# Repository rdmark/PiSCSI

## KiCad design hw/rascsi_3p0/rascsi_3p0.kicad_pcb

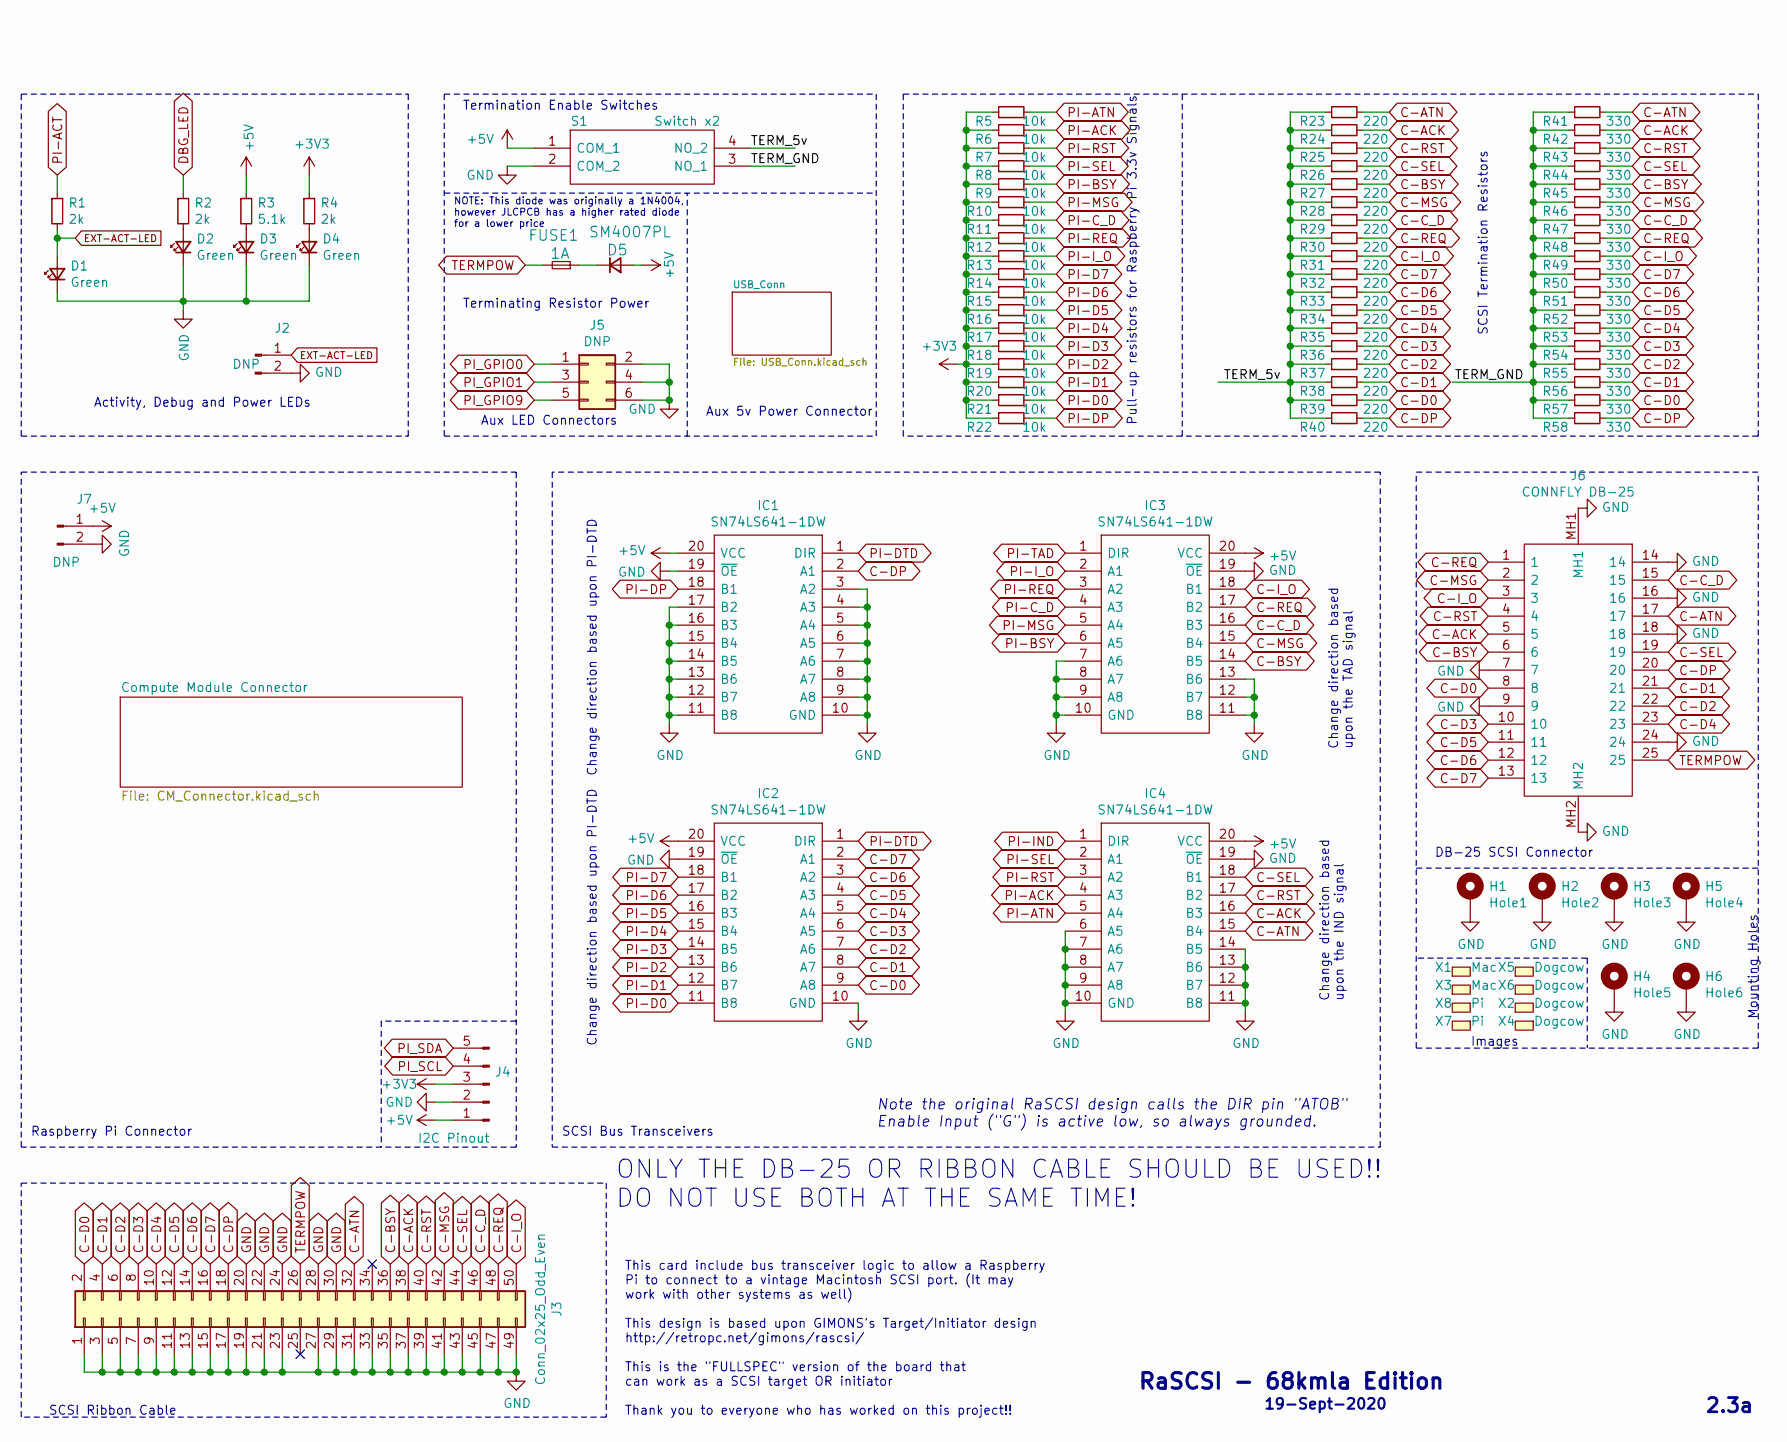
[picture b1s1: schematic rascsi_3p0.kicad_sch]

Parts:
D1, D2, D3, D4: Green; LED_0805_2012Metric; Manufacturer_Part_Number C2297; LCSC C2297
D5: SM4007PL; D_SOD-123F; Manufacturer_Part_Number SM4007PL; LCSC C64898
FUSE1: 1A; Fuse_1206_3216Metric; Manufacturer_Part_Number 12B1100B; LCSC C182974
H1: Hole1; MountingHole_2.7mm_M2.5_Pad_Via; Manufacturer_Part_Number DNP; LCSC DNP
H2: Hole2; MountingHole_2.7mm_M2.5_Pad_Via; Manufacturer_Part_Number DNP; LCSC DNP
H3: Hole3; MountingHole_2.7mm_M2.5_Pad_Via; Manufacturer_Part_Number DNP; LCSC DNP
H4: Hole5; MountingHole_2.7mm_M2.5_Pad_Via; Manufacturer_Part_Number DNP; LCSC DNP
H5: Hole4; MountingHole_2.7mm_M2.5_Pad_Via; Manufacturer_Part_Number DNP; LCSC DNP
H6: Hole6; MountingHole_2.7mm_M2.5_Pad_Via; Manufacturer_Part_Number DNP; LCSC DNP
IC1, IC2, IC3, IC4: SN74LS641-1DW; SOIC127P1030X265-20N; Manufacturer_Part_Number SN74LS641-1DW; LCSC N/A
J2: DNP; PinHeader_1x02_P2.54mm_Horizontal; Manufacturer_Part_Number DNP; LCSC DNP
J3: Conn_02x25_Odd_Even; PinHeader_2x25_P2.54mm_Vertical; Manufacturer_Part_Number C30006; LCSC C30006
J4: I2C Pinout; PinSocket_1x05_P2.54mm_Vertical; Manufacturer_Part_Number C50950; LCSC C50950
J5: DNP; PinHeader_2x03_P2.54mm_Vertical; Manufacturer_Part_Number DNP; LCSC DNP
J6: CONNFLY DB-25; 57489011; Manufacturer_Part_Number DS1037-25FNAKT74-0CC; LCSC C77838
J7: DNP; PinHeader_1x02_P2.54mm_Vertical; Manufacturer_Part_Number DNP; LCSC DNP
R1, R2, R4: 2k; R_0402_1005Metric; Manufacturer_Part_Number 0402WGF2001TCE; LCSC C4109
R3: 5.1k; R_0402_1005Metric; Manufacturer_Part_Number 0402WGF5101TCE; LCSC C25905
R5, R6, R7, R8, R9, R10, R11, R12, R13, R14, R15, R16, R17, R18, R19, R20, R21, R22: 10k; R_0402_1005Metric; Manufacturer_Part_Number 0402WGF1002TCE; LCSC C25744
R23, R24, R25, R26, R27, R28, R29, R30, R31, R32, R33, R34, R35, R36, R37, R38, R39, R40: 220; R_0402_1005Metric; Manufacturer_Part_Number 0402WGF2200TCE; LCSC C25091
R41, R42, R43, R44, R45, R46, R47, R48, R49, R50, R51, R52, R53, R54, R55, R56, R57, R58: 330; R_0402_1005Metric; Manufacturer_Part_Number 0402WGF3300TCE; LCSC C25104
S1: Switch x2; SOIC127P812X230-4N; Manufacturer_Part_Number DSHP02TSGET; LCSC C40735
X1, X3: Mac; mac_happy_small; Manufacturer_Part_Number N/A; LCSC N/A
X2, X4, X5, X6: Dogcow; dogcow; Manufacturer_Part_Number N/A; LCSC N/A
X7: Pi; pi_logo; Manufacturer_Part_Number N/A; LCSC N/A
X8: Pi; scsi_logo; Manufacturer_Part_Number N/A; LCSC N/A

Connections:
+3V3: J4.3, R4.1, R5.1, R6.1, R7.1, R8.1, R9.1, R10.1, R11.1, R12.1, R13.1, R14.1, R15.1, R16.1, R17.1, R18.1, R19.1, R20.1, R21.1, R22.1; also elsewhere on the board
+5V: D5.2 (A), IC1.20 (VCC), IC2.20 (VCC), IC3.20 (VCC), IC4.20 (VCC), J4.1, J7.1, R3.1, S1.1 (COM_1); also elsewhere on the board
/TERM_5v: R23.1, R24.1, R25.1, R26.1, R27.1, R28.1, R29.1, R30.1, R31.1, R32.1, R33.1, R34.1, R35.1, R36.1, R37.1, R38.1, R39.1, R40.1, S1.4 (NO_2)
/TERM_GND: R41.1, R42.1, R43.1, R44.1, R45.1, R46.1, R47.1, R48.1, R49.1, R50.1, R51.1, R52.1, R53.1, R54.1, R55.1, R56.1, R57.1, R58.1, S1.3 (NO_1)
C-ACK: IC4.16 (B3), J3.38, J6.5, R24.2, R42.2
C-ATN: IC4.15 (B4), J3.32, J6.17, R23.2, R41.2
C-BSY: IC3.14 (B5), J3.36, J6.6, R27.2, R45.2
C-C_D: IC3.16 (B3), J3.46, J6.15, R29.2, R47.2
C-D0: IC2.9 (A8), J3.2, J6.8, R39.2, R57.2
C-D1: IC2.8 (A7), J3.4, J6.21, R38.2, R56.2
C-D2: IC2.7 (A6), J3.6, J6.22, R37.2, R55.2
C-D3: IC2.6 (A5), J3.8, J6.10, R36.2, R54.2
C-D4: IC2.5 (A4), J3.10, J6.23, R35.2, R53.2
C-D5: IC2.4 (A3), J3.12, J6.11, R34.2, R52.2
C-D6: IC2.3 (A2), J3.14, J6.12, R33.2, R51.2
C-D7: IC2.2 (A1), J3.16, J6.13, R32.2, R50.2
C-DP: IC1.2 (A1), J3.18, J6.20, R40.2, R58.2
C-I_O: IC3.18 (B1), J3.50, J6.3, R31.2, R49.2
C-MSG: IC3.15 (B4), J3.42, J6.2, R28.2, R46.2
C-REQ: IC3.17 (B2), J3.48, J6.1, R30.2, R48.2
C-RST: IC4.17 (B2), J3.40, J6.4, R25.2, R43.2
C-SEL: IC4.18 (B1), J3.44, J6.19, R26.2, R44.2
DBG_LED: R2.1; also elsewhere on the board
EXT-ACT-LED: D1.2 (A), J2.1, R1.2
GND: D1.1 (K), D2.1 (K), D3.1 (K), D4.1 (K), H1.1, H2.1, H3.1, H4.1, H5.1, H6.1, IC1.3 (A2), IC1.4 (A3), IC1.5 (A4), IC1.6 (A5), IC1.7 (A6), IC1.8 (A7), IC1.9 (A8), IC1.10 (GND), IC1.11 (B8), IC1.12 (B7), IC1.13 (B6), IC1.14 (B5), IC1.15 (B4), IC1.16 (B3), IC1.17 (B2), IC1.19 (~OE), IC2.10 (GND), IC2.19 (~OE), IC3.7 (A6), IC3.8 (A7), IC3.9 (A8), IC3.10 (GND), IC3.11 (B8), IC3.12 (B7), IC3.13 (B6), IC3.19 (~OE), IC4.6 (A5), IC4.7 (A6), IC4.8 (A7), IC4.9 (A8), IC4.10 (GND), IC4.11 (B8), IC4.12 (B7), IC4.13 (B6), IC4.14 (B5), IC4.19 (~OE), J2.2, J3.1, J3.3, J3.5, J3.7, J3.9, J3.11, J3.13, J3.15, J3.17, J3.19, J3.20, J3.21, J3.22, J3.23, J3.24, J3.27, J3.28, J3.29, J3.30, J3.31, J3.33, J3.35, J3.37, J3.39, J3.41, J3.43, J3.45, J3.47, J3.49, J4.2, J5.2, J5.4, J5.6, J6.7, J6.9, J6.14, J6.16, J6.18, J6.24, J6.MH1, J6.MH2, J7.2, S1.2 (COM_2); also elsewhere on the board
unnamed: D2.2 (A), R2.2
unnamed: D3.2 (A), R3.2
unnamed: D4.2 (A), R4.2
unnamed: D5.1 (K), FUSE1.1
PI-ACK: IC4.4 (A3), R6.2; also elsewhere on the board
PI-ACT: R1.1; also elsewhere on the board
PI-ATN: IC4.5 (A4), R5.2; also elsewhere on the board
PI-BSY: IC3.6 (A5), R9.2; also elsewhere on the board
PI-C_D: IC3.4 (A3), R11.2; also elsewhere on the board
PI-D0: IC2.11 (B8), R21.2; also elsewhere on the board
PI-D1: IC2.12 (B7), R20.2; also elsewhere on the board
PI-D2: IC2.13 (B6), R19.2; also elsewhere on the board
PI-D3: IC2.14 (B5), R18.2; also elsewhere on the board
PI-D4: IC2.15 (B4), R17.2; also elsewhere on the board
PI-D5: IC2.16 (B3), R16.2; also elsewhere on the board
PI-D6: IC2.17 (B2), R15.2; also elsewhere on the board
PI-D7: IC2.18 (B1), R14.2; also elsewhere on the board
PI-DP: IC1.18 (B1), R22.2; also elsewhere on the board
PI-DTD: IC1.1 (DIR), IC2.1 (DIR); also elsewhere on the board
PI-IND: IC4.1 (DIR); also elsewhere on the board
PI-I_O: IC3.2 (A1), R13.2; also elsewhere on the board
PI-MSG: IC3.5 (A4), R10.2; also elsewhere on the board
PI-REQ: IC3.3 (A2), R12.2; also elsewhere on the board
PI-RST: IC4.3 (A2), R7.2; also elsewhere on the board
PI-SEL: IC4.2 (A1), R8.2; also elsewhere on the board
PI-TAD: IC3.1 (DIR); also elsewhere on the board
PI_GPIO0: J5.1; also elsewhere on the board
PI_GPIO1: J5.3; also elsewhere on the board
PI_GPIO9: J5.5; also elsewhere on the board
PI_SCL: J4.4; also elsewhere on the board
PI_SDA: J4.5; also elsewhere on the board
TERMPOW: FUSE1.2, J3.26, J6.25

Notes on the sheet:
Raspberry Pi Connector
SCSI Ribbon Cable
Activity, Debug and Power LEDs
NOTE: This diode was originally a 1N4004, however JLCPCB has a higher rated diode for a lower price
Termination Enable Switches
Terminating Resistor Power
Aux LED Connectors
SCSI Bus Transceivers
Change direction based upon PI-DTD
ONLY THE DB-25 OR RIBBON CABLE SHOULD BE USED!! DO NOT USE BOTH AT THE SAME TIME!
This card include bus transceiver logic to allow a Raspberry Pi to connect to a vintage Macintosh SCSI port. (It may work with other systems as well) This design is based upon GIMONS's Target/Initiator design http://retropc.net/gimons/rascsi/ This is the "FULLSPEC" version of the board that can wor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
Aux 5v Power Connector
Note the original RaSCSI design calls the DIR pin "ATOB" Enable Input ("G") is active low, so always grounded.
Pull-up resistors for Raspberry Pi 3.3v Signals
RaSCSI - 68kmla Edition
19-Sept-2020
Change direction based upon the IND signal
Change direction based upon the TAD signal
DB-25 SCSI Connector
Images
SCSI Termination Resistors
2.3a
Mounting Holes

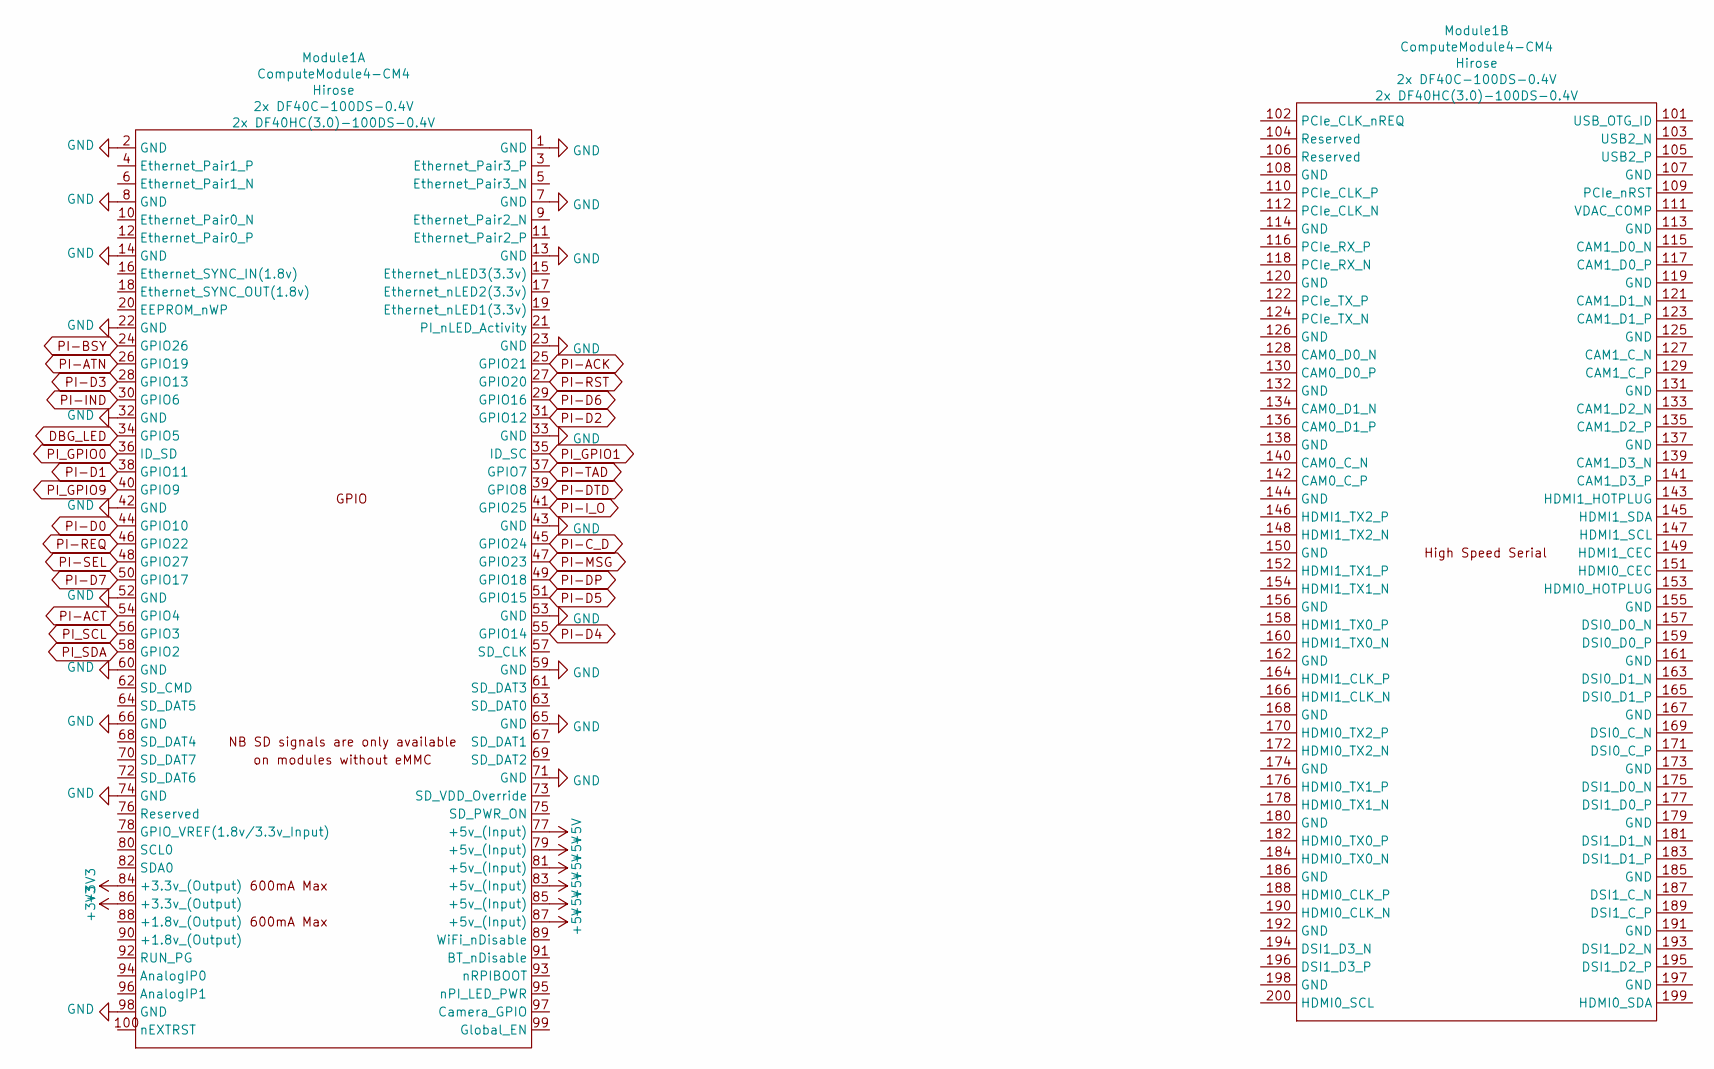
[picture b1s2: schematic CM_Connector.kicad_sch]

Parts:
Module1: ComputeModule4-CM4; Raspberry-Pi-4-Compute-Module; MPN 2x DF40C-100DS-0.4V; Digi-Key_PN 2x H11615CT-ND

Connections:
+3V3: Module1.84 (+3.3v_(Output)), Module1.86 (+3.3v_(Output)); also elsewhere on the board
+5V: Module1.77 (+5v_(Input)), Module1.79 (+5v_(Input)), Module1.81 (+5v_(Input)), Module1.83 (+5v_(Input)), Module1.85 (+5v_(Input)), Module1.87 (+5v_(Input)); also elsewhere on the board
DBG_LED: Module1.34 (GPIO5); also elsewhere on the board
GND: Module1.1 (GND), Module1.2 (GND), Module1.7 (GND), Module1.8 (GND), Module1.13 (GND), Module1.14 (GND), Module1.22 (GND), Module1.23 (GND), Module1.32 (GND), Module1.33 (GND), Module1.42 (GND), Module1.43 (GND), Module1.52 (GND), Module1.53 (GND), Module1.59 (GND), Module1.60 (GND), Module1.65 (GND), Module1.66 (GND), Module1.71 (GND), Module1.74 (GND), Module1.98 (GND); also elsewhere on the board
PI-ACK: Module1.25 (GPIO21); also elsewhere on the board
PI-ACT: Module1.54 (GPIO4); also elsewhere on the board
PI-ATN: Module1.26 (GPIO19); also elsewhere on the board
PI-BSY: Module1.24 (GPIO26); also elsewhere on the board
PI-C_D: Module1.45 (GPIO24); also elsewhere on the board
PI-D0: Module1.44 (GPIO10); also elsewhere on the board
PI-D1: Module1.38 (GPIO11); also elsewhere on the board
PI-D2: Module1.31 (GPIO12); also elsewhere on the board
PI-D3: Module1.28 (GPIO13); also elsewhere on the board
PI-D4: Module1.55 (GPIO14); also elsewhere on the board
PI-D5: Module1.51 (GPIO15); also elsewhere on the board
PI-D6: Module1.29 (GPIO16); also elsewhere on the board
PI-D7: Module1.50 (GPIO17); also elsewhere on the board
PI-DP: Module1.49 (GPIO18); also elsewhere on the board
PI-DTD: Module1.39 (GPIO8); also elsewhere on the board
PI-IND: Module1.30 (GPIO6); also elsewhere on the board
PI-I_O: Module1.41 (GPIO25); also elsewhere on the board
PI-MSG: Module1.47 (GPIO23); also elsewhere on the board
PI-REQ: Module1.46 (GPIO22); also elsewhere on the board
PI-RST: Module1.27 (GPIO20); also elsewhere on the board
PI-SEL: Module1.48 (GPIO27); also elsewhere on the board
PI-TAD: Module1.37 (GPIO7); also elsewhere on the board
PI_GPIO0: Module1.36 (ID_SD); also elsewhere on the board
PI_GPIO1: Module1.35 (ID_SC); also elsewhere on the board
PI_GPIO9: Module1.40 (GPIO9); also elsewhere on the board
PI_SCL: Module1.56 (GPIO3); also elsewhere on the board
PI_SDA: Module1.58 (GPIO2); also elsewhere on the board

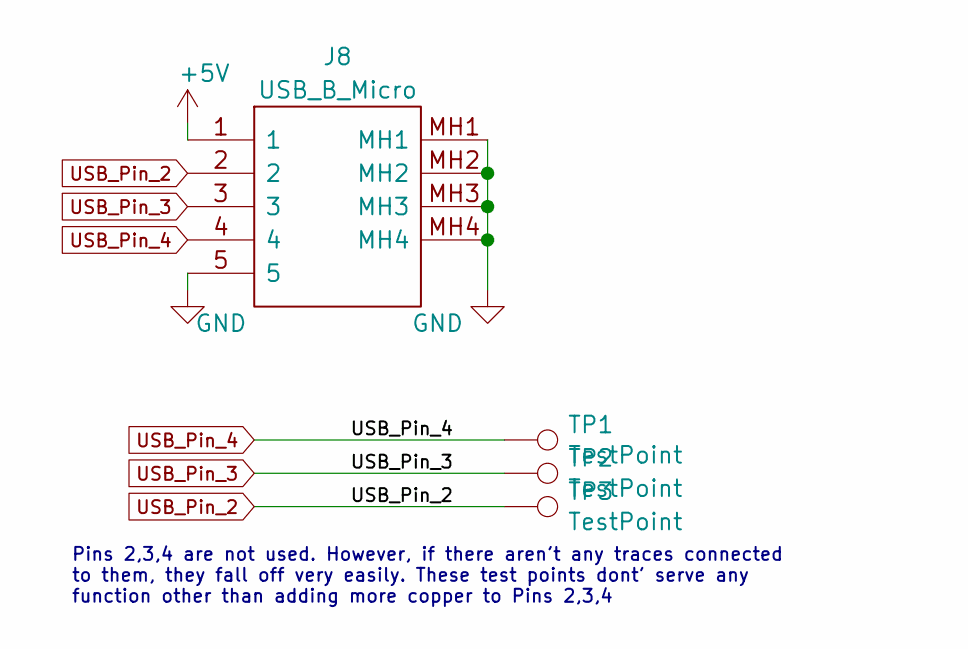
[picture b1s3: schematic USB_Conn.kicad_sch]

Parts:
J8: USB_B_Micro; U254051N4BH806; Manufacturer_Part_Number U254-051N-4BH806; LCSC C319170
TP1, TP2, TP3: TestPoint; TestPoint_Pad_D1.0mm; Manufacturer_Part_Number N/A; LCSC N/A

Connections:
+5V: J8.1; also elsewhere on the board
GND: J8.5, J8.MH1, J8.MH2, J8.MH3, J8.MH4; also elsewhere on the board
USB_Pin_2: J8.2, TP3.1
USB_Pin_3: J8.3, TP2.1
USB_Pin_4: J8.4, TP1.1

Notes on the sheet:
Pins 2,3,4 are not used. However, if there aren't any traces connected to them, they fall off very easily. These test points dont' serve any function other than adding more copper to Pins 2,3,4

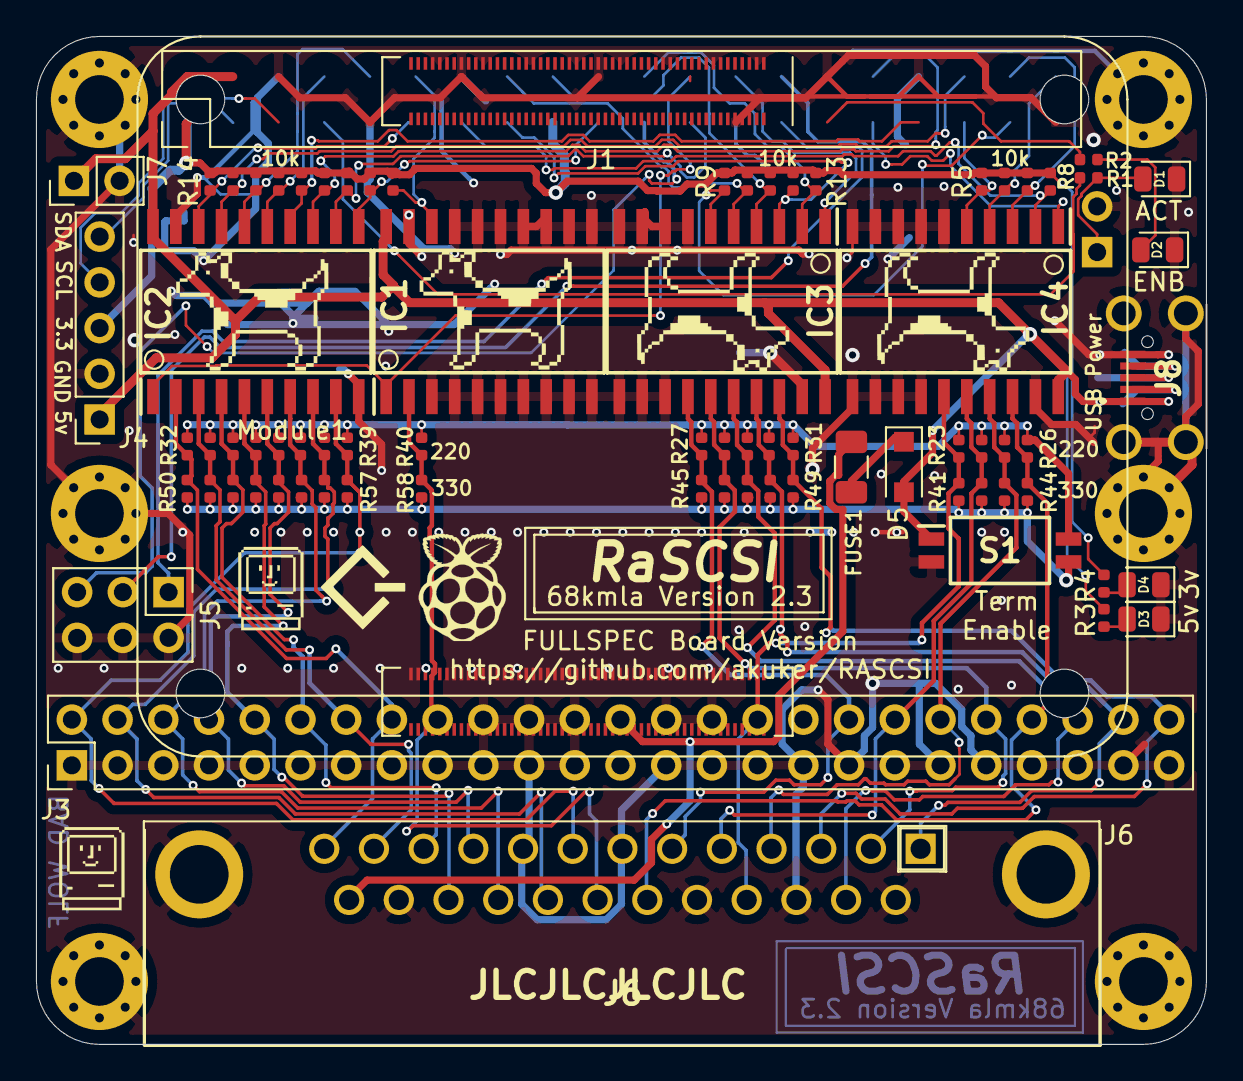
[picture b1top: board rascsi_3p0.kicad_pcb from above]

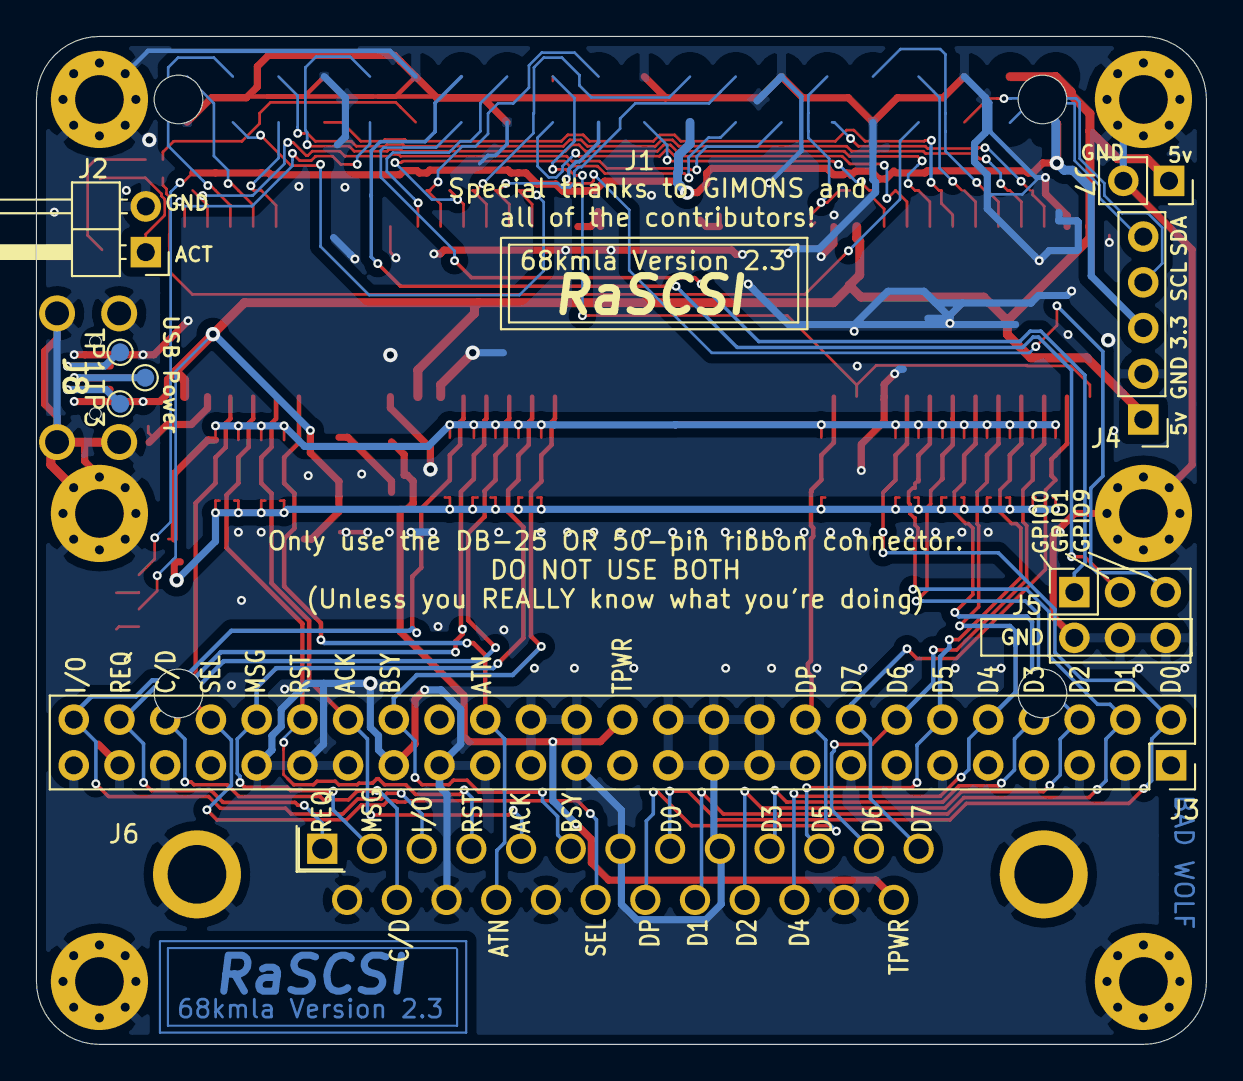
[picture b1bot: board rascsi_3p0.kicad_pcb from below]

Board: 2 copper layers, 65.0 x 56.0 mm, 94 parts (4 on the bottom side), 60 nets.

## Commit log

2020-08-09 Broke HUGE disk.cpp file into smaller class files
2020-08-09 #16 Fixed makefile clean rule and added xm6.h to disk.h so that all Disk functions are included for non-bm build
2020-08-09 Print out build date of software and note that this is the 68kmla version on the startup banner
2020-08-09 #16 Reorganized files
2020-08-10 #16 Lots more refactoring.... doesn't work anymore... work in progress
2020-08-16 Additional updates
2020-08-16 Additional changes
2020-08-16 Additional changes.... command interface works?
2020-08-17 Cleanup translation and add header
2020-08-17 Fix warning
2020-08-17 Temporarily remove the device type checking. It doesn't handle the different HD types properly
2020-08-17 Delay locking the manager until we have a transaction in progress
2020-08-17 Added some debug code
2020-08-28 Start to back out some changes. Just include command processing changes
2020-08-28 Added global git ignore file
2020-08-29 Fixed issue in PHP code where if the type is specified as hd, rascsi ignores the file name to figure out the type
2020-08-29 Fixed the install rule
2020-12-28 Pull meaningful changes from large_file_breakup branch
2021-03-23 Initial draft of Compute Module board
2021-06-01 Dealing with Duplicate ID issues
    re:issue 101, when attaching multiple images (1+2 or 2+4 or 3+6) rascsi can report the second ID is a duplicate. We can fix this by dropping UnitNum from 2 to 1
2021-07-29 Bridgeutils are needed for daynaport
2021-08-19 Create WLAN bridge if eth0 is not up
2021-08-19 Log update
2021-08-19 Logging update
